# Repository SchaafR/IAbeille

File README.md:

# IABEILLES — Système de surveillance de ruches intelligent

**IABEILLES** est une solution IoT (Internet des Objets) développée à Polytech Sorbonne pour protéger les colonies d'abeilles contre la prédation des frelons asiatiques. Le système utilise l'intelligence artificielle pour la détection visuelle et sonore, tout en transmettant des données environnementales via le réseau LoRaWAN.

---

## Table des Matières
* [Présentation](#-présentation)
* [Spécifications Matérielles](#-spécifications-matérielles)
* [Installation Logicielle](#-installation-logicielle)
* [Configuration Réseau (LoRaWAN/TTN)](#-configuration-réseau)
* [Mise en Service](#-mise-en-service)
* [Équipe](#-équipe)

---

## Présentation

### Mission
Transformer des mesures physiques en **informations exploitables** pour les apiculteurs et chercheurs. Le système surveille en temps réel :
* **Détection visuelle** (IA) : Identification des abeilles et frelons.
* **Détection sonore** : Analyse de l'activité acoustique.
* **Environnement** : Température, humidité et luminosité.

### Architecture de communication
`Capteurs (I2C/Analog)` ➔ `ESP32S3 / Nano BLE` ➔ `Module LoRa E5` ➔ `Passerelle LoRaWAN` ➔ `TTN` ➔ `Bleep (Dashboard)`

---

## Spécifications Matérielles

| Composant | Rôle Principal |
| :--- | :--- |
| **XIAO ESP32S3 Sense** | Cœur de l'IA (Vision) & Caméra |
| **Arduino Nano BLE Sense** | Analyse sonore & Gestion des capteurs |
| **Module LoRa E5** | Communication longue portée |
| **DHT22 & BH1750** | Monitoring Température/Humidité/Lumière |
| **Panneau Solaire & LiPo** | Autonomie énergétique (3.7V 1000mAh) |
| **PCB Custom** | Interconnexion et robustesse |

---

## Installation Logicielle

### 1. Prérequis
* [Arduino IDE](https://www.arduino.cc/en/software)
* Support de carte **ESP32 by Espressif Systems** (via le gestionnaire de cartes).
* Support de carte **Arduino Mbed OS Nano Boards**.

### 2. Récupération du projet
```bash
git clone https://github.com/SchaafR/IAbeille.git
```

### 3. Installation des Librairies Custom (IA)
Les modèles d'inférence sont fournis sous forme d'archives `.zip` dans le dossier `/data`.
1. Localisez votre dossier Arduino (ex: `Documents/Arduino/libraries`).
2. Décompressez-y les fichiers suivants :
   - `BeeGuardAI_Hornet_Bee_Bees_G1V2_inferencing.zip`
   - `Hornets_lib_3.zip`
3. Redémarrez l'IDE Arduino.

### 4. Dépendances Standard
Installez via le **Library Manager** d'Arduino :
* `DHT sensor library`
* `BH1750`

---

## Configuration Réseau

### The Things Network (TTN)
Le module LoRa E5 utilise l'activation **OTAA**.
1. **Créer une application** sur [TTN Console](https://console.cloud.thethings.network/).
2. **Enregistrer l'appareil** avec les identifiants présents dans le code source :
   - `DevEUI`
   - `AppEUI` / `JoinEUI`
   - `AppKey`
3. **Payload Formatter** : Utilisez le script JavaScript situé dans `/src/payload_formatter` pour décoder les trames hexadécimales en données lisibles.

---

## Mise en Service

### Flashage des cartes
1. Ouvrez `COM_N_AI.ino` dans Arduino IDE.
2. Connectez le **XIAO ESP32S3**.
3. Sélectionnez le port correspondant et le type de carte **XIAO_ESP32S3**.
4. Cliquez sur **Upload** (→).
5. Répétez l'opération pour l'Arduino Nano avec le fichier `hornet_lib_3.ino`.

### Déploiement physique
> [!IMPORTANT]
> Vérifiez l'étanchéité du boîtier et le serrage des presse-étoupes avant l'installation en extérieur.

1. Actionnez le bouton **On/Off**.
2. Un **bip sonore (0.5s)** confirme l'initialisation du système.
3. Vérifiez la LED de charge (Panneau Solaire/Batterie).
4. Surveillez l'onglet **Live Data** sur TTN pour confirmer la réception des premières trames.

---

## Équipe (Rédacteurs)

* **Léo Dupuy**
* **Amine Filahi**
* **Benoit Lavieville**
* **Marguerite Massinga**
* **Rémy Schaaf**

---

## Remerciements
Projet réalisé dans le cadre de la 4ème année à **Polytech Sorbonne**. Merci à l'équipe pédagogique et aux encadrants pour leur soutien technique et méthodologique.

## Contacte
En cas de problème ou de questions, vous pouvez nous contacter à l'adresse : schaarem@gmail.com

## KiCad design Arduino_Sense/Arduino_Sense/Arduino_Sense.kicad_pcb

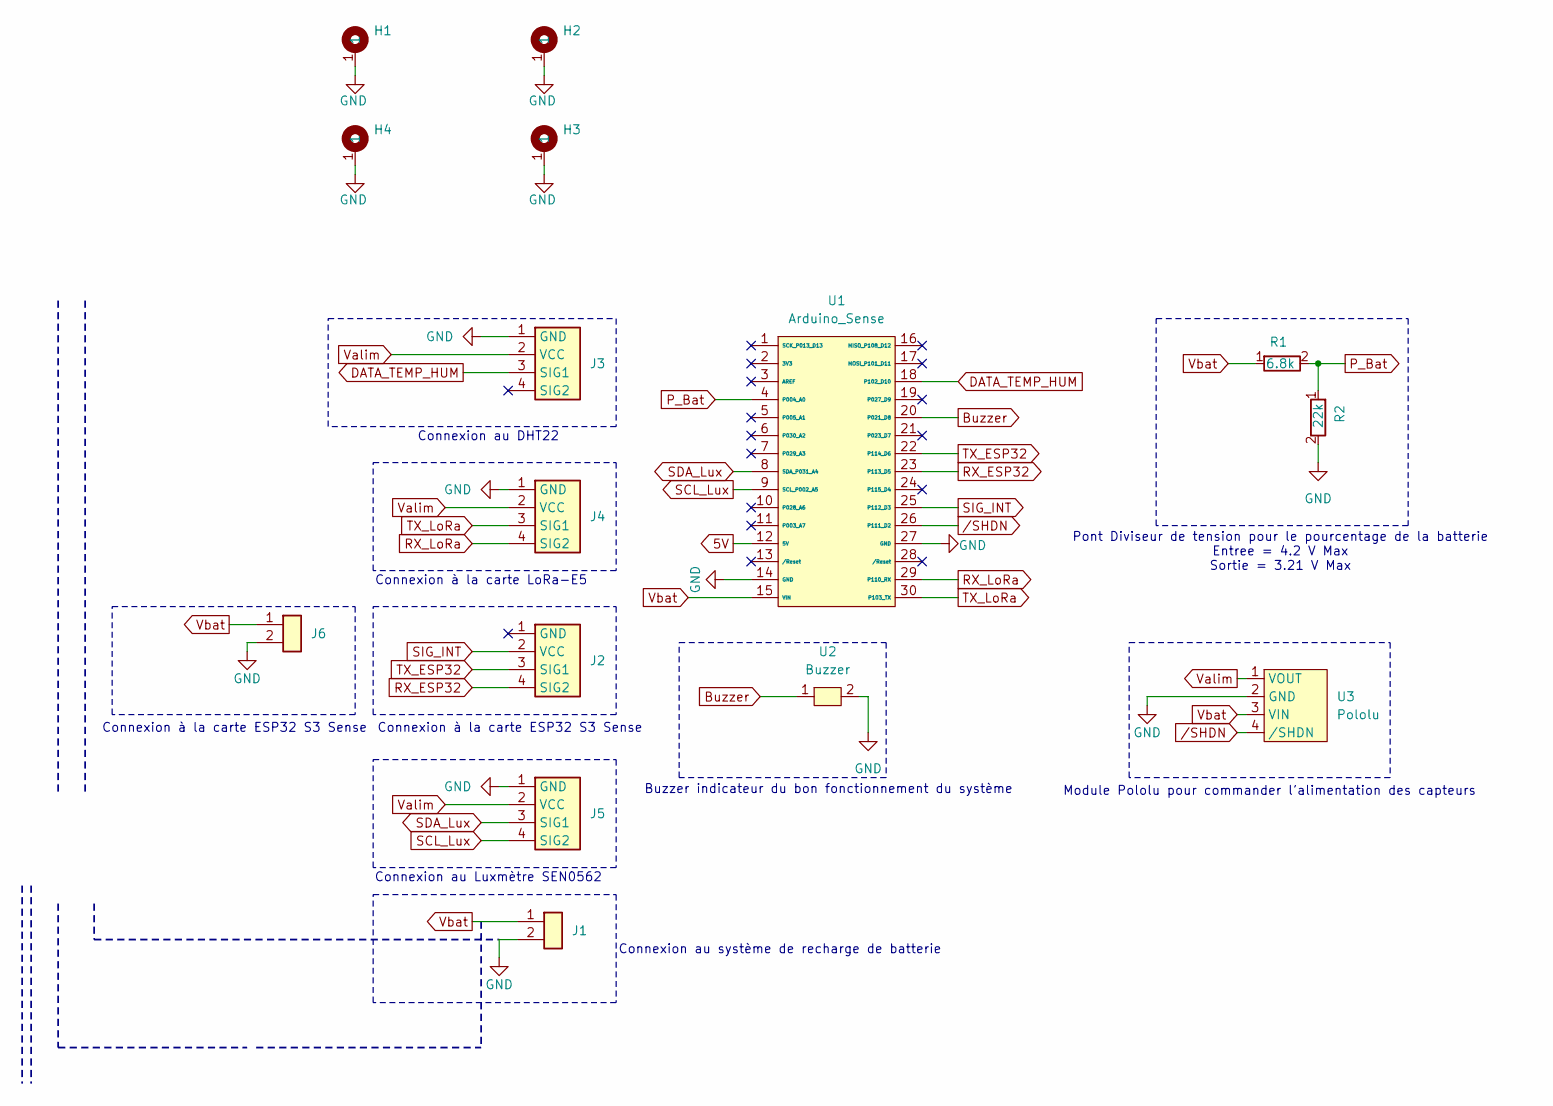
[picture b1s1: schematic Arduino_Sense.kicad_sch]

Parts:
H1, H2, H3, H4: Mounting_Hole
J1, J6: PinSocket_1x02_P2.00mm_Vertical
J2, J3, J4, J5: PinSocket_1x04_P2.00mm_Vertical
R1: 6.8k; R
R2: 22k; R
U1: Arduino_Sense
U2: Buzzer
U3: Pololu

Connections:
5V: U1.12 (5V)
Buzzer: U1.20 (P021_D8), U2.1
DATA_TEMP_HUM: J3.3 (SIG1), U1.18 (P102_D10)
GND: H1.1, H2.1, H3.1, H4.1, J1.2, J3.1 (GND), J4.1 (GND), J5.1 (GND), J6.2, R2.2, U1.14 (GND), U1.27 (GND), U2.2, U3.2 (GND)
P_Bat: R1.2, R2.1, U1.4 (P004_A0)
RX_ESP32: J2.4 (SIG2), U1.23 (P113_D5)
RX_LoRa: J4.4 (SIG2), U1.29 (P110_RX)
SCL_Lux: J5.4 (SIG2), U1.9 (SCL_P002_A5)
SDA_Lux: J5.3 (SIG1), U1.8 (SDA_P031_A4)
SIG_INT: J2.2 (VCC), U1.25 (P112_D3)
TX_ESP32: J2.3 (SIG1), U1.22 (P114_D6)
TX_LoRa: J4.3 (SIG1), U1.30 (P103_TX)
Valim: J3.2 (VCC), J4.2 (VCC), J5.2 (VCC), U3.1 (VOUT)
Vbat: J1.1, J6.1, R1.1, U1.15 (VIN), U3.3 (VIN)
/SHDN: U1.26 (P111_D2), U3.4 (/SHDN)

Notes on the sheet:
Connexion à la carte ESP32 S3 Sense
Connexion au Luxmètre SEN0562
Buzzer indicateur du bon fonctionnement du système
Connexion à la carte ESP32 S3 Sense
Pont Diviseur de tension pour le pourcentage de la batterie Entree = 4.2 V Max Sortie = 3.21 V Max
Connexion au DHT22
Connexion à la carte LoRa-E5
Module Pololu pour commander l'alimentation des capteurs
Connexion au système de recharge de batterie

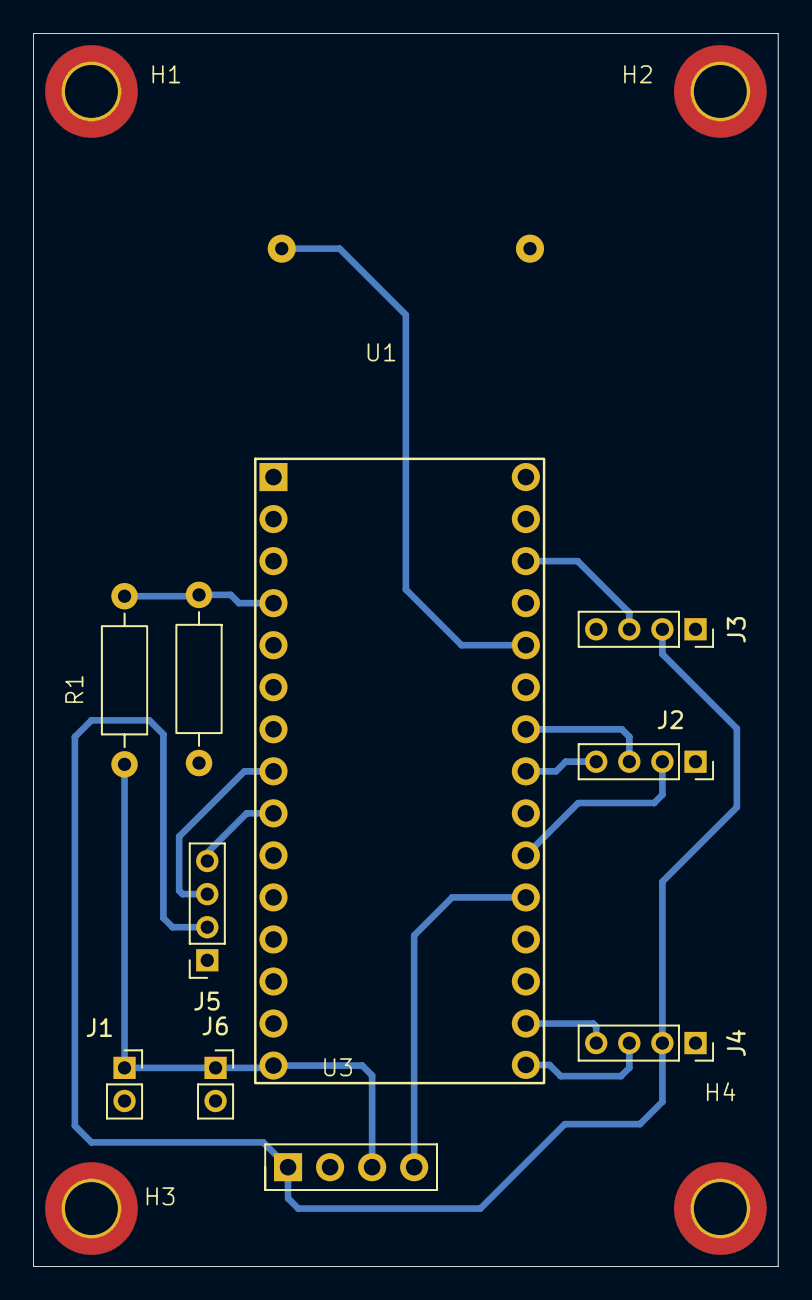
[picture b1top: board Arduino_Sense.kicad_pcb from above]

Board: 2 copper layers, 45.0 x 74.5 mm, 15 parts (0 on the bottom side), 14 nets.

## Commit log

2026-02-19 file structure of the project
2026-02-23 Model Fonctionnel avec FOMO96x96
2026-03-02 Template fonctionnel pour les capteurs
    Template pour utilisation des capteurs sur arduino MKR WAN 1310. Ce template est à adapter pour arduino nano BLE
    Sont intégré: luxmètre, DHT11, Buzzer.
    Les métriques remontées : température, humidité, luminosité, indicateur Sonor de la mise en fonctionnement de l'équipement.
2026-03-03 ajout d'une fonctionnalité de threshold
2026-03-03 IA Hornet en 240
2026-03-07 Communication unidirectionnelle Bit Banging
    Communication unidirectionnelle Bit Banging XIAO (Master) Arduino NANO BLE (Slave)
2026-03-07 présentation sprint 1
2026-03-08 Schéma fonctionnel
2026-03-08 Hardware
2026-03-08 Hardware + schema synoptique
2026-03-10 Communication bidirectionnel bit Banging
    Communication bidirectionnel avec payload au bon format :
    [A5] [5A] [TYPE] [LEN] [PAYLOAD...] [CHK]
    A5 5A : préambule
    TYPE : type de message
    LEN : taille payload
    PAYLOAD : données
2026-03-13 Intercommunication avec comptage
    Prototype fonctionnel : intercommunication + comptage simple.
    Code prêt pour l’intégration du deep sleep.
    À faire : adapter les pins selon le pin planner et remplacer le modèle IA par fomo-best-results.
2026-03-16 Connexion à TTN et test des webhook
2026-03-17 Code et Image des mesures effectuées sur les capteurs et l'arduino
2026-03-17 architecture complete
    ajout des capteurs
    ajout du lien lora WAN
2026-03-24 comptage inte
2026-03-24 différent model utilisé
2026-03-28 ComNANO_BLE_V0.1
    Machine à états v0.1
2026-04-02 final version
2026-04-02 comptage + Sleep fusionné
2026-04-06 Code final
2026-04-10 Version finale
2026-04-10 version final
    suppression deep sleep, commande de wake up supprimée, from de de la trame modifié
2026-04-16 Articles
2026-04-16 Revise README for project details and structure
    Updated project description and folder structure details in README.
2026-04-16 Présentation finale
2026-04-16 Update README with project features and structure
2026-04-26 Create payload formateur
    ajout du payload formateur pour TTN
2026-04-27 Rename hardware.zip to doc/hardware.zip
    déplacement du fichier
2026-04-27 Rename payload formateur to payload_formatter
2026-04-29 Ajout d'un guide utilisateur complet

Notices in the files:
README.md:
License: MIT
